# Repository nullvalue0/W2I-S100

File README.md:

S-100 Board Version of Mike Arnold's W2I (WDI to IDE adapter), for emulating up to four 11Mb IMI7710A drives. It is compatible with CDOS, Z80 Cromix, 68000 Cromix and Cromix Plus. It works with the Cromemco WDI and WDI-II controller.

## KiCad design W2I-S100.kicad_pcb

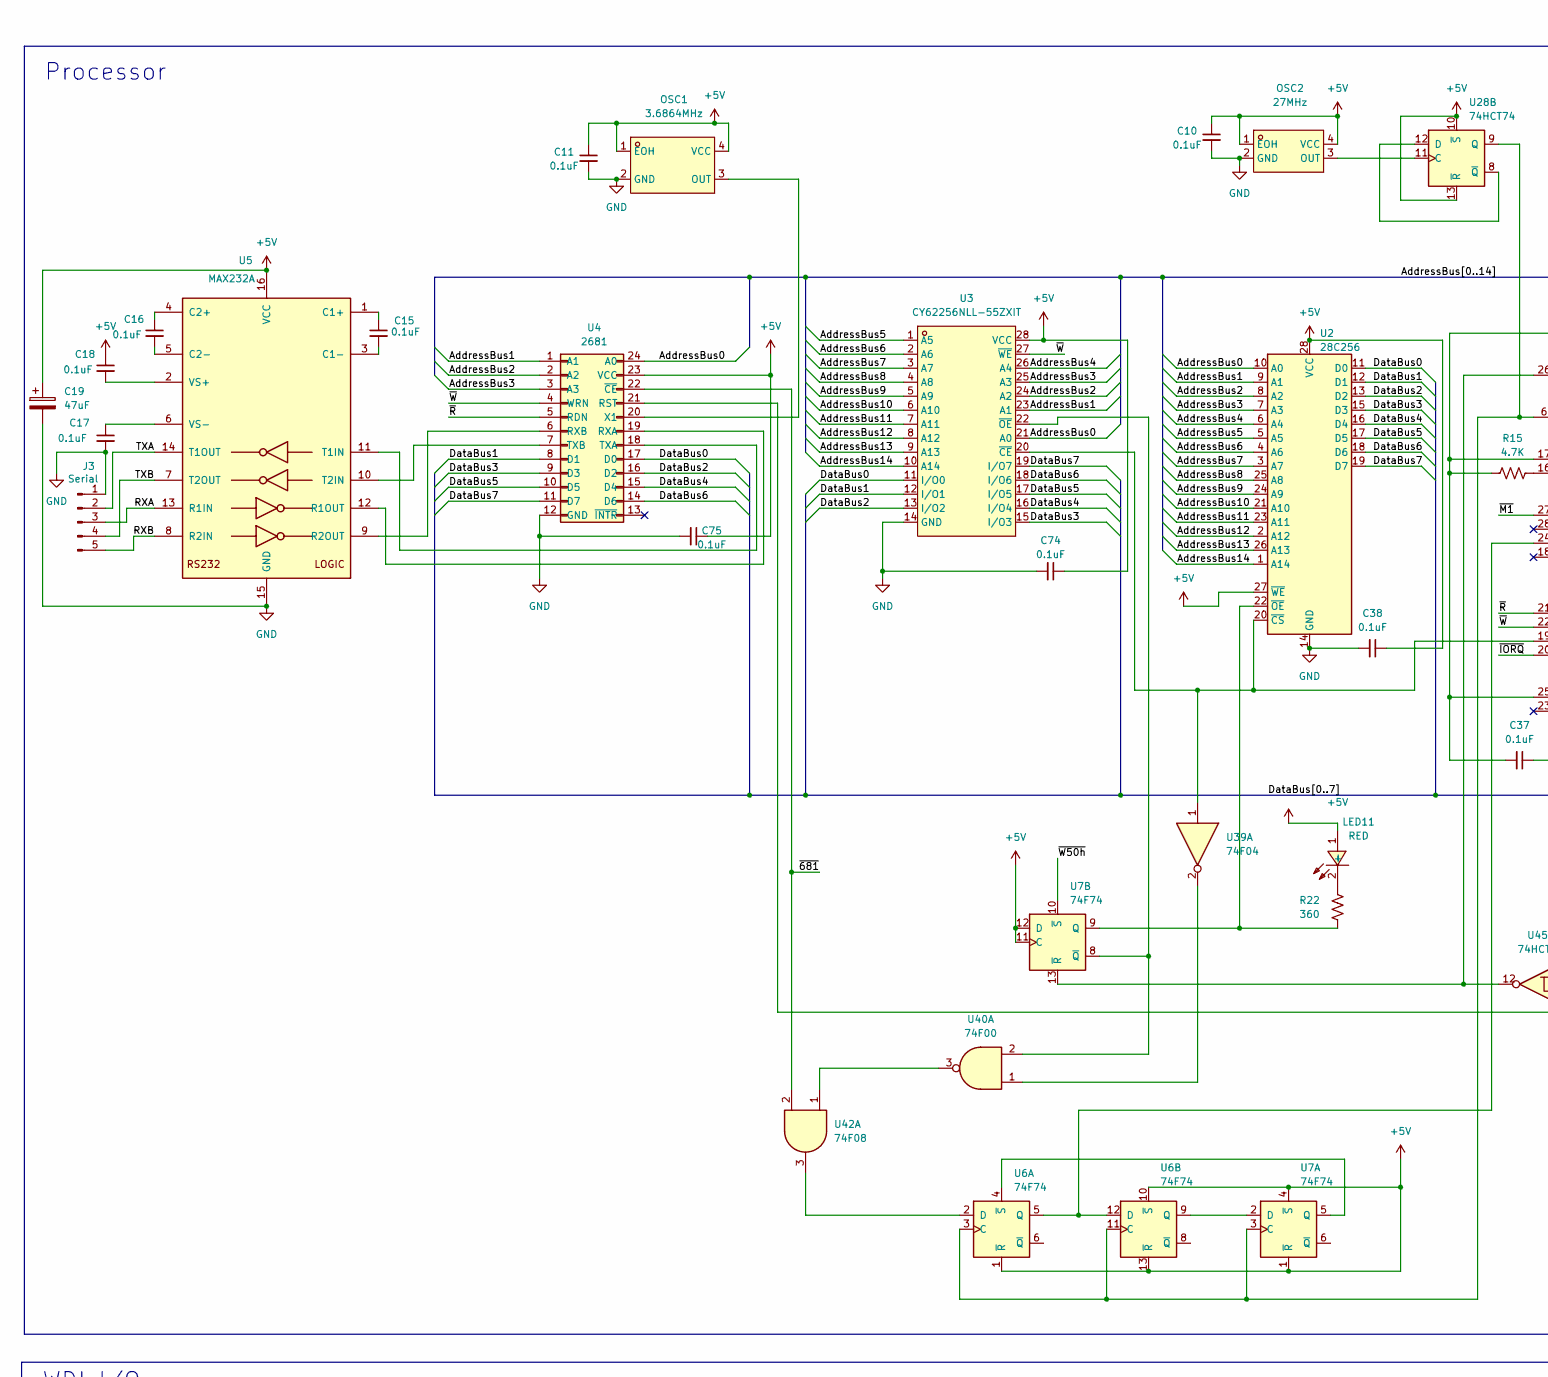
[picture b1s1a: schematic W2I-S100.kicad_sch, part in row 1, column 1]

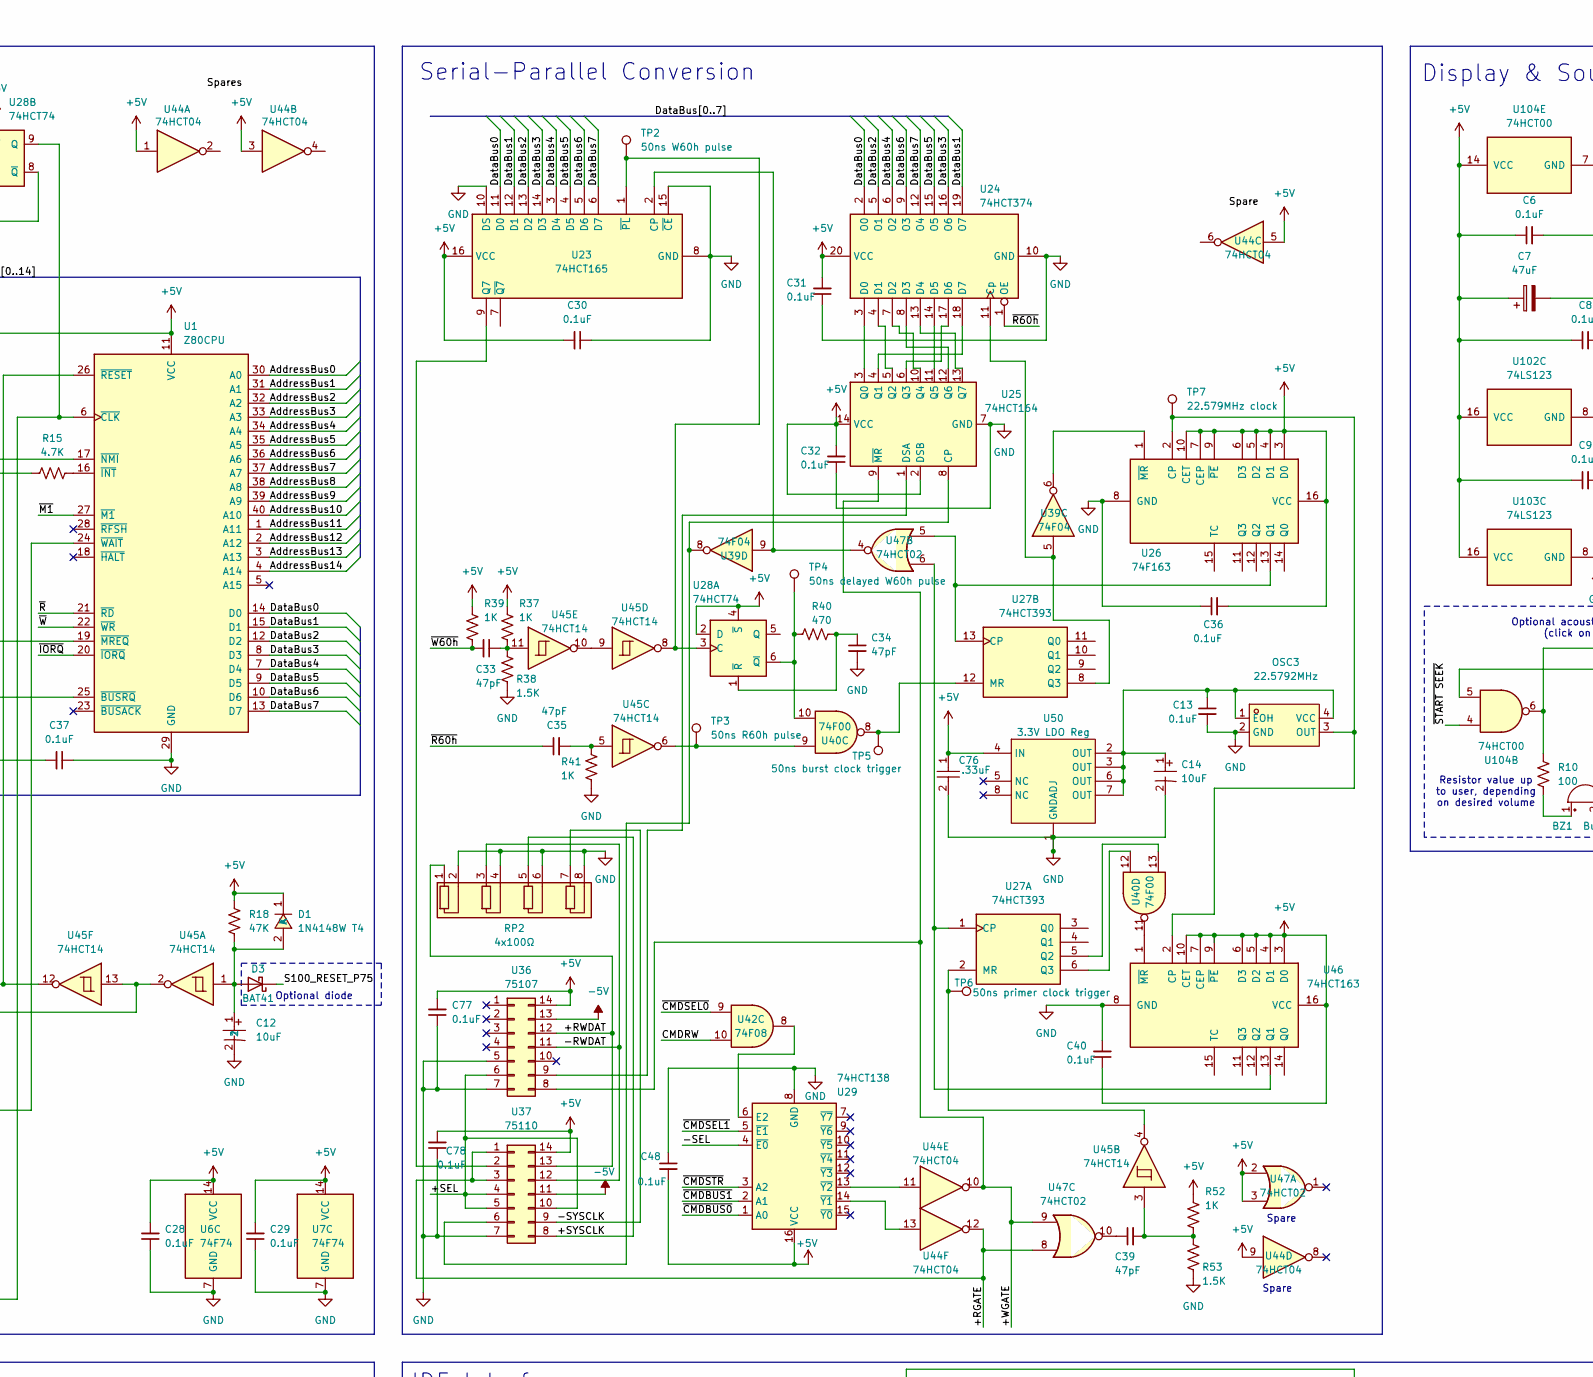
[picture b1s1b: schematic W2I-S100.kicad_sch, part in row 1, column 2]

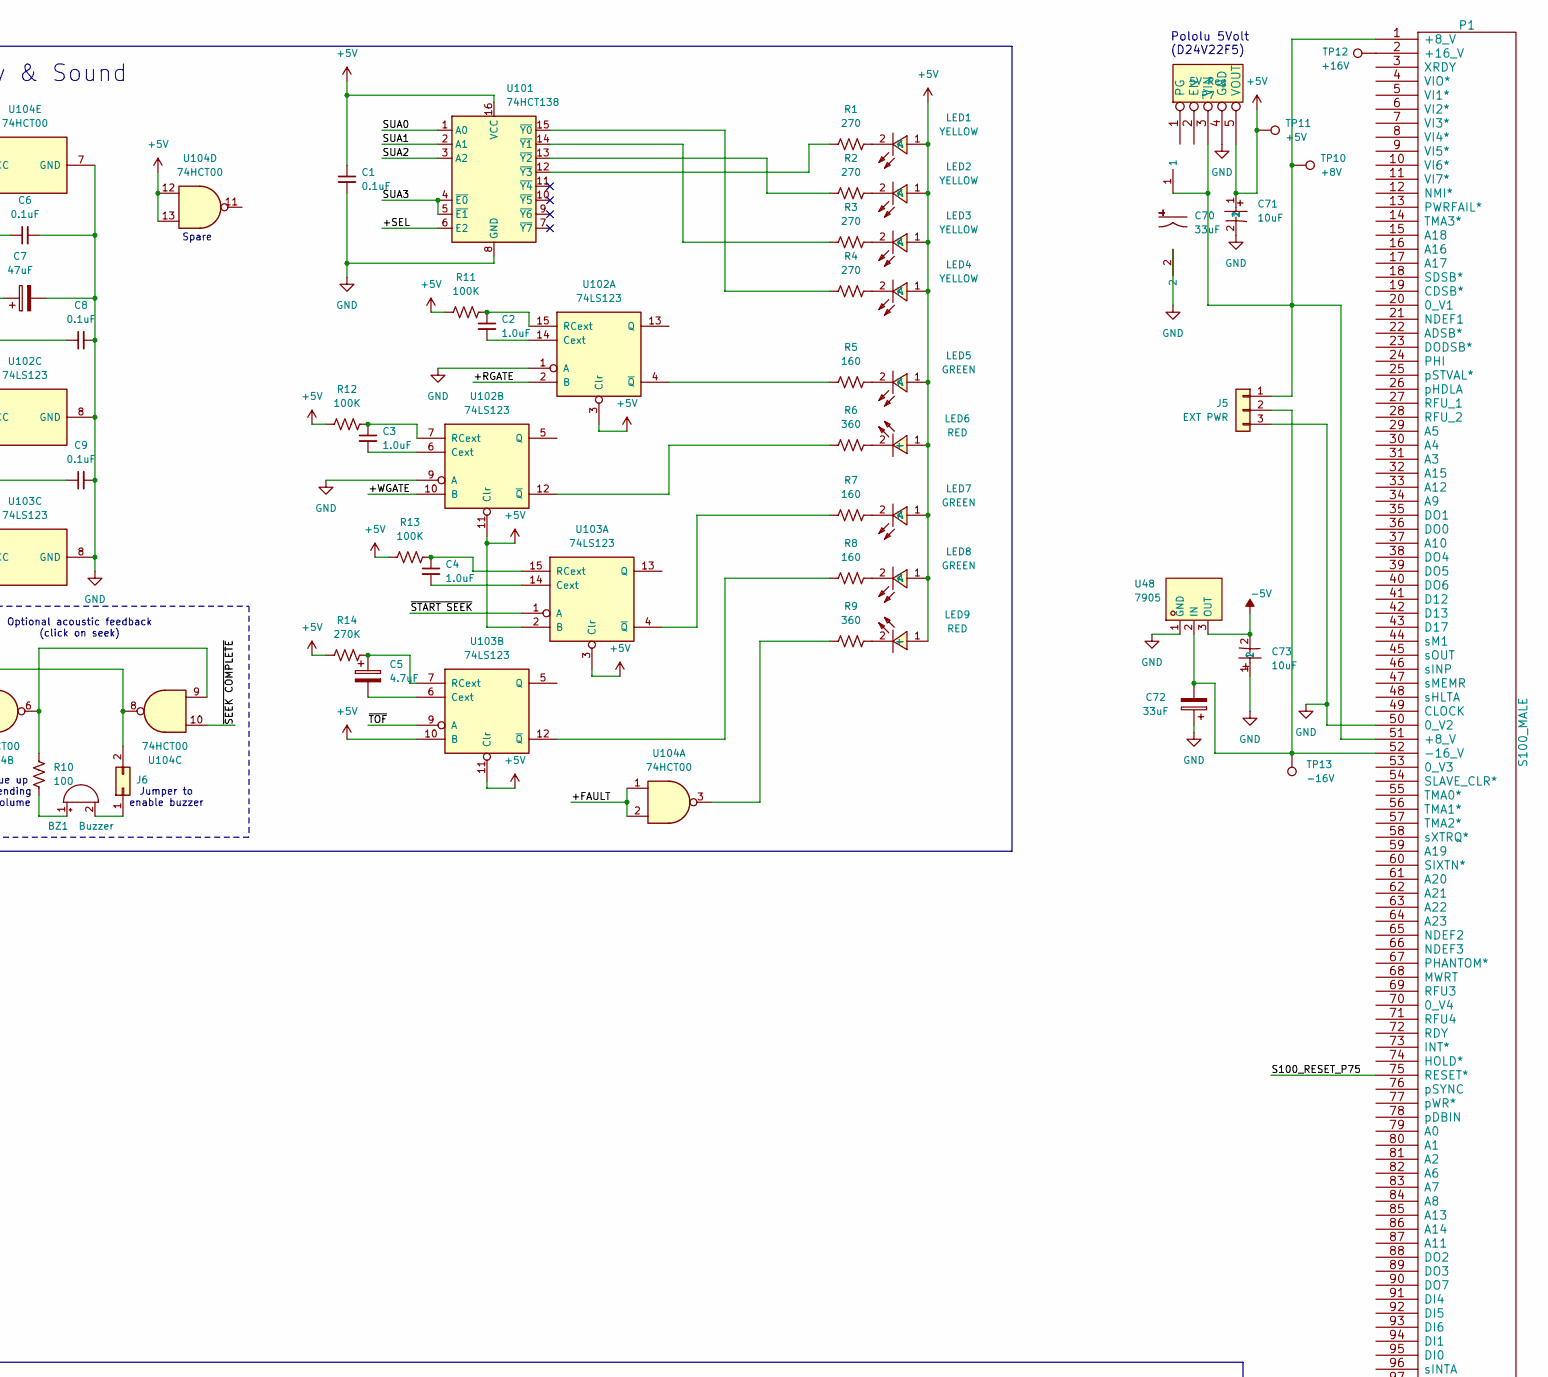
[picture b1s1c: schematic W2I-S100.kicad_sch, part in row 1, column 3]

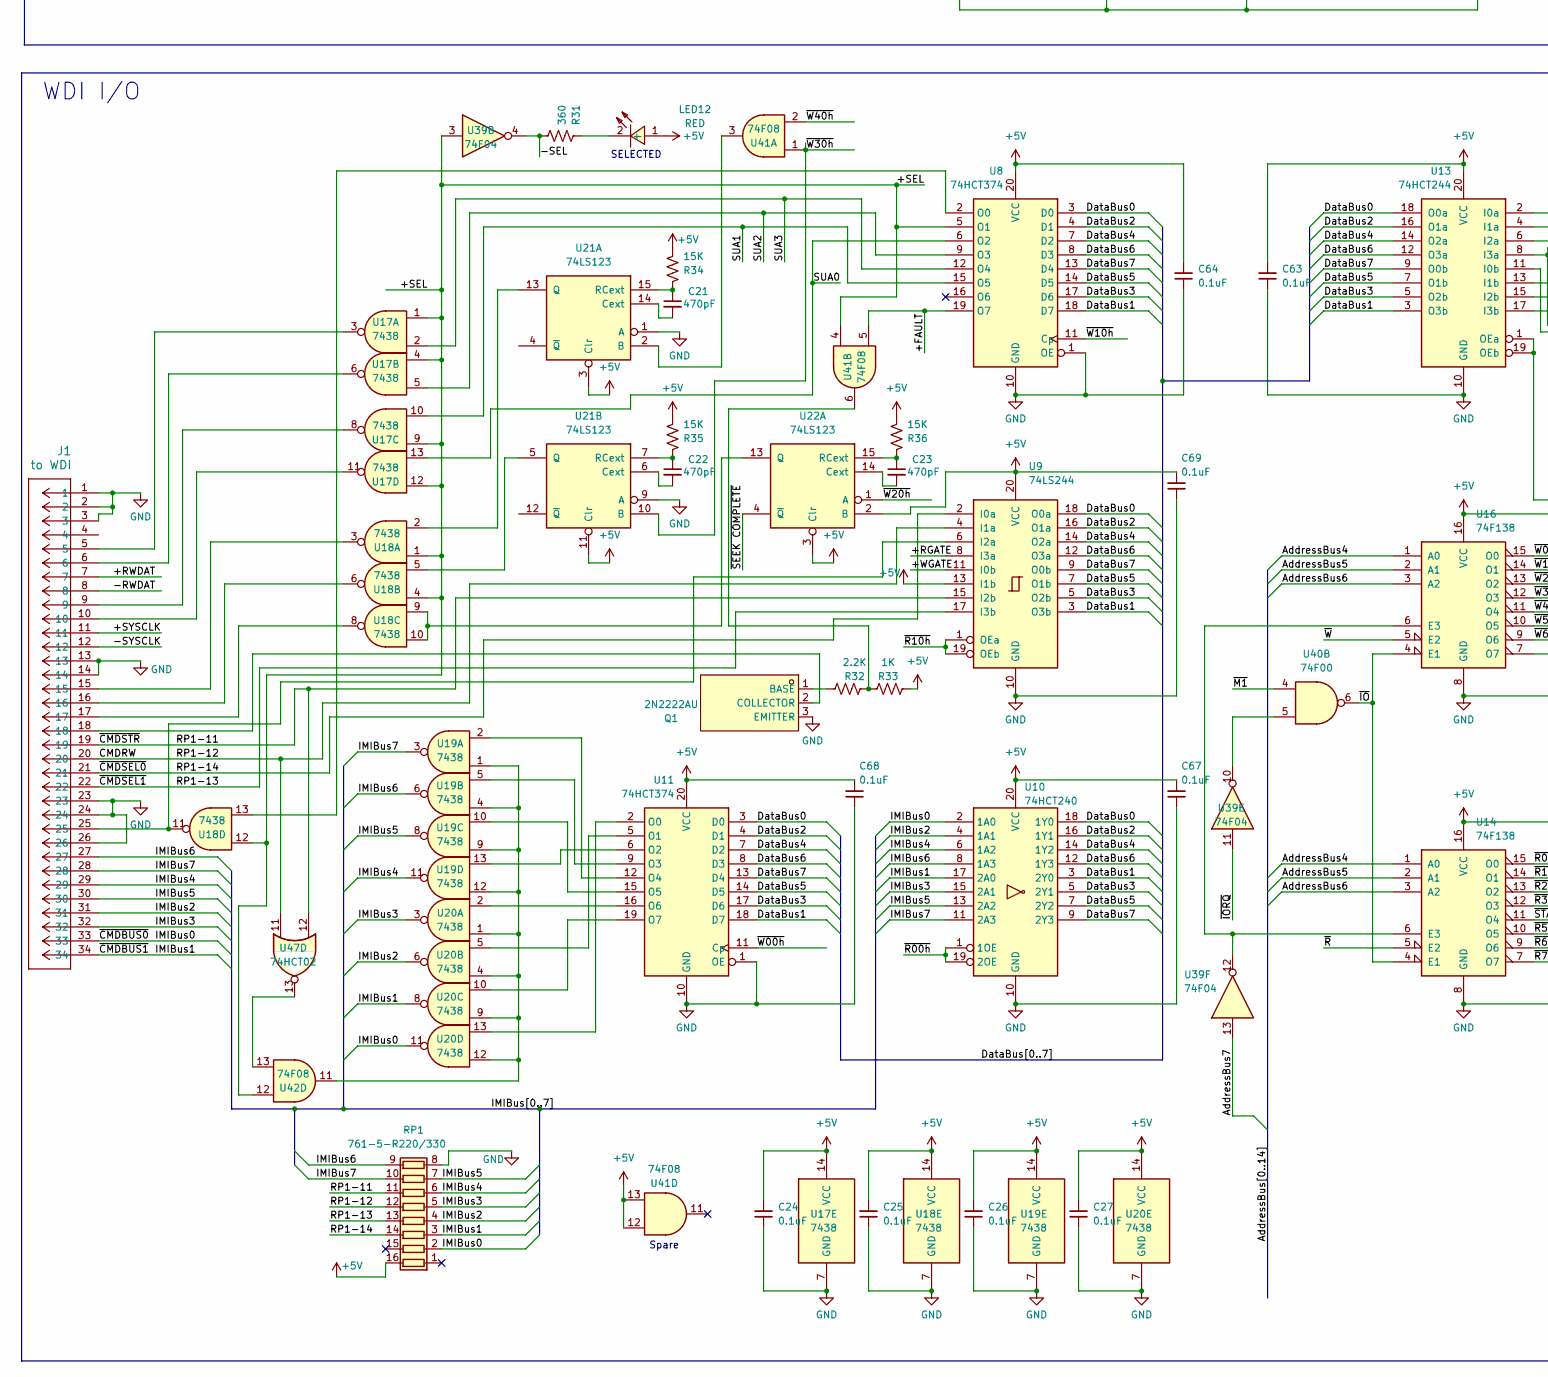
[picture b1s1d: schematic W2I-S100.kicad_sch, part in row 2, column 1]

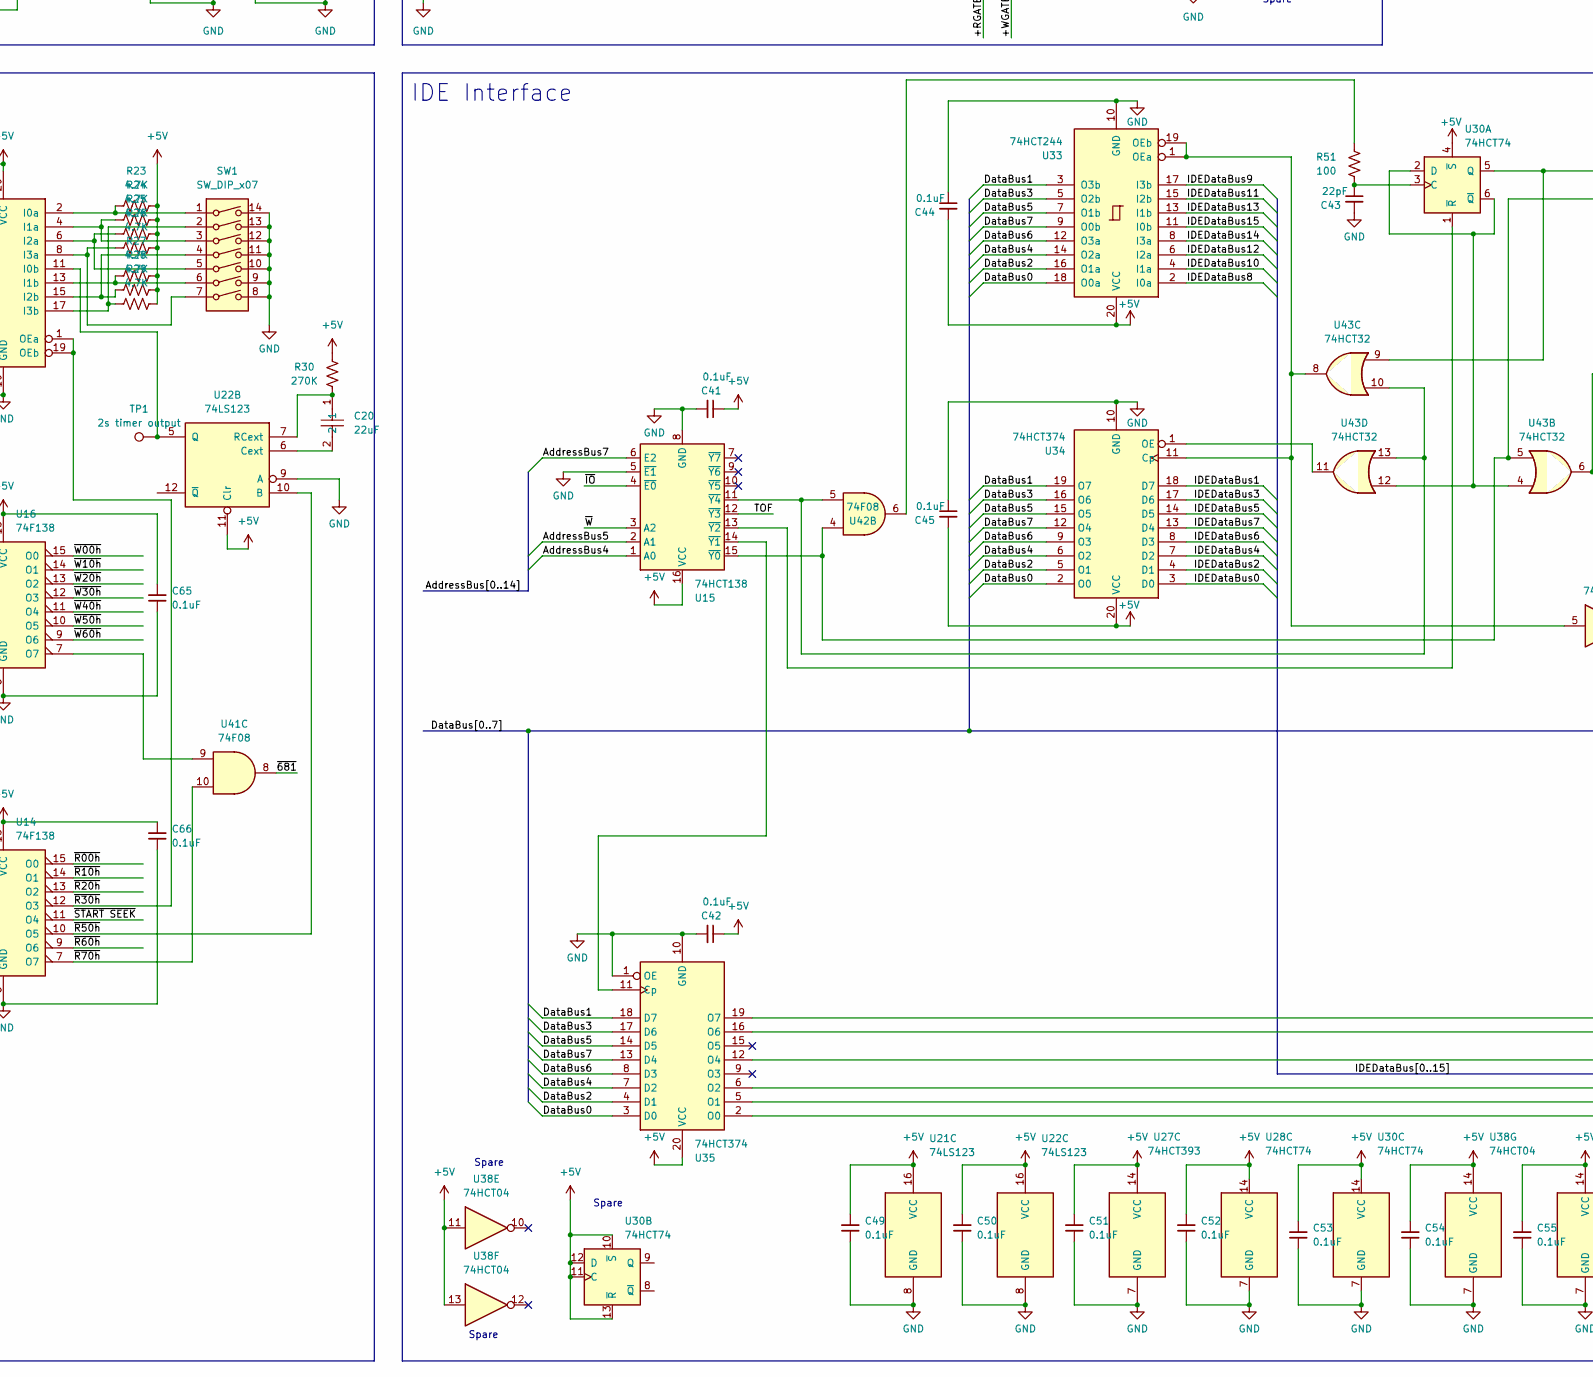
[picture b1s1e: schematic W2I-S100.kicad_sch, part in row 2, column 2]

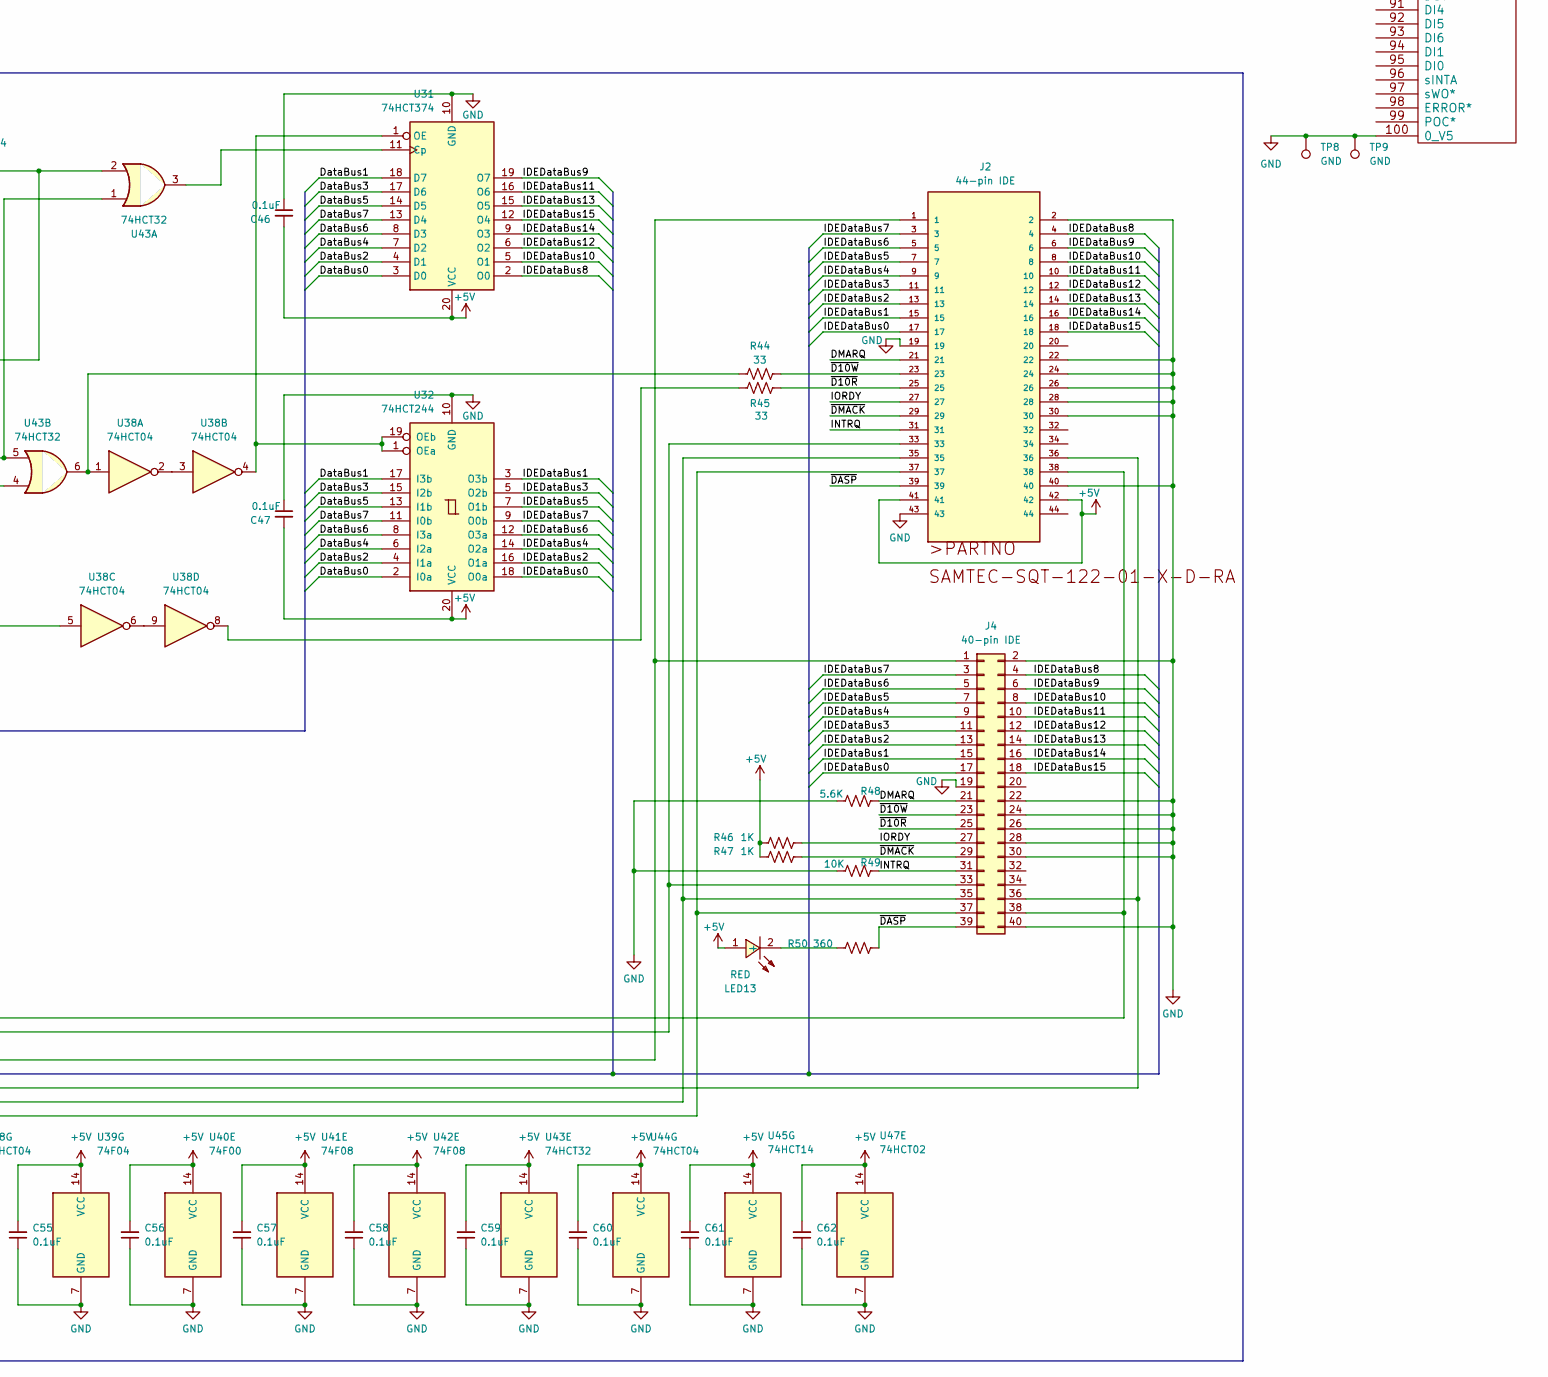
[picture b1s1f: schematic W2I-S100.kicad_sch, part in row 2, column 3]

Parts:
BZ1: Buzzer; Buzzer_12x9.5RM7.6
C1, C6, C8, C9, C10, C11, C13, C15, C16, C17, C18, C24, C25, C26, C27, C28, C29, C30, C31, C32, C36, C37, C38, C40, C41, C42, C44, C45, C46, C47, C48, C49, C50, C51, C52, C53, C54, C55, C56, C57, C58, C59, C60, C61, C62, C63, C64, C65, C66, C67, C68, C69, C74, C75, C77, C78: 0.1uF; C0603; LCSC Part C1590
C2, C3, C4: 1.0uF; C0603; LCSC Part C29936
C5: 4.7uF; CAP-SMD_BD4.0-L4.3-W4.3-LS5.3-FD; LCSC Part C264246
C7, C19: 47uF; CAP-SMD_BD6.3-L6.6-W6.6-FD; LCSC Part C141425
C12, C14, C71, C73: 10uF; CAP-SMD_BD4.0-L4.3-W4.3-FD; LCSC Part C3343
C20: 22uF; C0603; LCSC Part C2762594
C21, C22, C23: 470pF; C0603; LCSC Part C519395
C33, C34, C35, C39: 47pF; C0603; LCSC Part C519392
C43: 22pF; C0603; LCSC Part C519390
C70, C72: 33uF; CAP-SMD_BD6.3-L6.6-W6.6-FD; LCSC Part C249892
C76: .33uF; C0603; LCSC Part C1615
D1: 1N4148W T4; SOD-123_L2.8-W1.8-LS3.7-RD; LCSC Part C2099
D3: BAT41; D_DO-35_SOD27_P7.62mm_Horizontal
J1: to WDI; IDC-Header_2x17_P2.54mm_Vertical
J2: 44-pin IDE; SAMTEC-SQT-122-01-X-D-RA
J3: Serial; PinHeader_1x05_P2.54mm_Vertical
J4: 40-pin IDE; IDC-Header_2x20_P2.54mm_Vertical
J5: EXT PWR; PinHeader_1x03_P2.54mm_Vertical
J6: Jumper to enable buzzer; PinHeader_2x01_P2.54mm_Vertical
LED1, LED2, LED3, LED4: YELLOW; LED0805-R-RD; LCSC Part C84261
LED5, LED7, LED8: GREEN; LED0805-R-RD; LCSC Part C84260
LED6, LED9, LED11, LED12, LED13: RED; LED0805-R-RD; LCSC Part C84256
OSC1: 3.6864MHz; OSC-SMD_4P-L7.0-W5.0-BL-2; LCSC Part C1851439
OSC2: 27MHz; OSC-SMD_4P-L7.0-W5.0-BL-2; LCSC Part C1851667
OSC3: 22.5792MHz; OSC-SMD_4P-L7.0-W5.0-BL-2; LCSC Part C7431407
P1: S100_MALE
P7: 5V Reg; PinHeader_1x05_P2.54mm_Vertical
Q1: 2N2222AU; SOT-89-3_L4.5-W2.4-P1.50-LS4.0-BR; LCSC Part C21714170
R1, R2, R3, R4: 270; R0603; LCSC Part C22966
R5, R7, R8: 160; R0603; LCSC Part C22814
R6, R9, R22, R31, R50: 360; R0603; LCSC Part C25194
R10: 100; R_Axial_DIN0207_L6.3mm_D2.5mm_P10.16mm_Horizontal
R11, R12, R13: 100K; R1206; LCSC Part C17900
R14, R30: 270K; R1206; LCSC Part C17940
R15, R23, R24, R25, R26, R27, R28, R29: 4.7K; R1206; LCSC Part C17936
R18: 47K; R1206; LCSC Part C25833
R32: 2.2K; R1206; LCSC Part C17948
R33, R37, R39, R41, R46, R47, R52: 1K; R1206; LCSC Part C1469
R34, R35, R36: 15K; R1206; LCSC Part C25828
R38, R53: 1.5K; R1206; LCSC Part C26030
R40: 470; R1206; LCSC Part C4502
R44, R45: 33; R1206; LCSC Part C18005
R48: 5.6K; R1206; LCSC Part C18028
R49: 10K; R1206; LCSC Part C17902
R51: 100; R1206; LCSC Part C17901
RP1: 761-5-R220/330; DIP-16_W7.62mm
RP2: 4x100Ω; R_Array_SIP8
SW1: SW_DIP_x07; DIP-14_W7.62mm
TP1: 2s timer output; TestPoint_THTPad_2.0x2.0mm_Drill1.0mm
TP2: 50ns W60h pulse; TestPoint_THTPad_2.0x2.0mm_Drill1.0mm
TP3: 50ns R60h pulse; TestPoint_THTPad_2.0x2.0mm_Drill1.0mm
TP4: 50ns delayed W60h pulse; TestPoint_THTPad_2.0x2.0mm_Drill1.0mm
TP5: 50ns burst clock trigger; TestPoint_THTPad_2.0x2.0mm_Drill1.0mm
TP6: 50ns primer clock trigger; TestPoint_THTPad_2.0x2.0mm_Drill1.0mm
TP7: 22.579MHz clock; TestPoint_THTPad_2.0x2.0mm_Drill1.0mm
TP8, TP9: GND; TestPoint_THTPad_2.0x2.0mm_Drill1.0mm
TP10: +8V; TestPoint_THTPad_2.0x2.0mm_Drill1.0mm
TP11: +5V; TestPoint_THTPad_2.0x2.0mm_Drill1.0mm
TP12: +16V; TestPoint_THTPad_2.0x2.0mm_Drill1.0mm
TP13: -16V; TestPoint_THTPad_2.0x2.0mm_Drill1.0mm
U1: Z80CPU; DIP-40_W15.24mm
U2: 28C256; DIP-28_W15.24mm
U3: CY62256NLL-55ZXIT; TSOP-28_L11.8-W8.0-P0.55-LS13.4-B_CYPRESS; LCSC Part C2759940
U4: 2681; DIP-24_W10.16mm
U5: MAX232A; DIP-16_W7.62mm
U6, U7: 74F74; SOIC-14_L8.7-W3.9-P1.27-LS6.0-BL; LCSC Part C6805
U8, U11, U24, U31, U34, U35: 74HCT374; SOP-20_L12.6-W5.3-P1.27-LS7.8-BL; LCSC Part C2677828
U9: 74LS244; SOP-20_L12.6-W5.3-P1.27-LS7.8-BL; LCSC Part C22374097
U10: 74HCT240; TSSOP-20_L6.5-W4.4-P0.65-LS6.5-BL; LCSC Part C543088
U13, U32, U33: 74HCT244; TSSOP-20_L6.5-W4.4-P0.65-LS6.4-BL; LCSC Part C131088
U14, U16: 74F138; DIP-16_W7.62mm
U15, U29, U101: 74HCT138; TSSOP-16_L5.0-W4.4-P0.65-LS6.4-BL; LCSC Part C8115
U17, U18, U19, U20: 7438; DIP-14_W7.62mm
U21, U22, U102, U103: 74LS123; SOIC-16_L9.9-W3.9-P1.27-LS6.0-BL; LCSC Part C234231
U23: 74HCT165; SOIC-16_L9.9-W3.9-P1.27-LS6.0-BL; LCSC Part C456131
U25: 74HCT164; TSSOP-14_L5.0-W4.4-P0.65-LS6.4-BL; LCSC Part C2908835
U26: 74F163; SOIC-16_L9.9-W3.9-P1.27-LS6.0-BL; LCSC Part C2675415
U27: 74HCT393; SO-14_L8.7-W3.9-P1.27-LS6.0-BL; LCSC Part C547642
U28, U30: 74HCT74; SO-14_L8.9-W3.9-P1.27-LS6.0-BL; LCSC Part C686657
U36: 75107; DIP-14_W7.62mm
U37: 75110; DIP-14_W7.62mm
U38, U44: 74HCT04; TSSOP-14_L5.0-W4.4-P0.65-LS6.4-BL; LCSC Part C131695
U39: 74F04; SOIC-14_L8.7-W3.9-P1.27-LS6.0-BL; LCSC Part C7159
U40: 74F00; SOIC-14_L8.7-W3.9-P1.27-LS6.0-BL; LCSC Part C7158
U41, U42: 74F08; SSOP-14_L6.2-W5.3-P0.65-LS7.8-BL-1; LCSC Part C4469192
U43: 74HCT32; TSSOP-14_L5.0-W4.4-P0.65-LS6.4-BL; LCSC Part C547595
U45: 74HCT14; TSSOP-14_L5.0-W4.4-P0.65-LS6.4-BL; LCSC Part C5968
U46: 74HCT163; SOIC-16_L9.9-W3.9-P1.27-LS6.0-BL; LCSC Part C2866759
U47: 74HCT02; SOIC-14_L8.7-W3.9-P1.27-LS6.0-BL; LCSC Part C471050
U48: 7905; TO-252-2_L6.6-W6.1-P4.57-LS10.1-BR-CW; LCSC Part C19273129
U50: 3.3V LDO Reg; SOIC-8_L5.0-W4.0-P1.27-LS6.0-BL; LCSC Part C7301
U104: 74HCT00; TSSOP-14_L5.0-W4.4-P0.65-LS6.4-BL; LCSC Part C8206

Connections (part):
+5V: C1.1, C6.1, C7.1, C8.1, C9.1, C10.1, C11.1, C18.1, C19.1, C24.2, C25.2, C26.2, C27.2, C28.2, C29.2, C30.2, C31.2, C32.2, C36.2, C37.2, C38.1, C40.1, C41.1, C42.1, C44.2, C45.2, C46.2, C47.2, C48.2, C49.2, C50.2, C51.2, C52.2, C53.2, C54.2, C55.2, C56.2, C57.2, C58.2, C59.2, C60.2, C61.2, C62.2, C63.2, C64.2, C65.2, C66.2, C67.2, C68.2, C69.2, C71.1, C74.1, C75.1, C76.1, C77.2, C78.2, D1.1 (K), J2.41, J2.42, LED1.1 (A), LED2.1 (A), LED3.1 (A), LED4.1 (A), LED5.1 (A), LED6.1 (+), LED7.1 (A), LED8.1 (A), LED9.1 (+), LED11.1 (+), LED12.1 (+), LED13.1 (+), OSC1.1 (EOH), OSC1.4 (VCC), OSC2.1 (EOH), OSC2.4 (VCC), P7.5 (VOUT), R11.2, R12.2, R13.2, R14.2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
-5V: C73.2, U36.13, U37.11, U48.3 (OUT)
/+FAULT: U8.19 (O7), U41.5, U104.1, U104.2
/+RGATE: U9.8 (I3a), U37.1, U37.3, U44.12, U47.8, U102.2 (B)
/+RWDAT: J1.7, RP2.1 (R1.1), U36.12, U37.13
/+SEL: U8.5 (O1), U17.1, U17.4, U17.9, U17.12, U18.1, U18.4, U18.12, U36.6, U37.4, U37.5, U37.10, U39.3, U41.4, U42.12, U101.6 (E2)
/+SYSCLK: J1.11, RP2.5 (R3.1), U37.8
/+WGATE: U9.11 (I0b), U25.9 (~MR), U36.8, U44.10, U47.9, U102.10 (B)
/-RWDAT: J1.8, RP2.3 (R2.1), U36.11, U37.12
/-SEL: R31.2, U29.4 (~E0), U39.4
/-SYSCLK: J1.12, RP2.7 (R4.1), U37.9
/AddressBus0: U1.30 (A0), U2.10 (A0), U3.21 (A0), U4.24 (A0)
/AddressBus1: U1.31 (A1), U2.9 (A1), U3.23 (A1), U4.1 (A1)
/AddressBus2: U1.32 (A2), U2.8 (A2), U3.24 (A2), U4.2 (A2)
/AddressBus3: U1.33 (A3), U2.7 (A3), U3.25 (A3), U4.3 (A3)
/AddressBus4: U1.34 (A4), U2.6 (A4), U3.26 (A4), U14.1 (A0), U15.1 (A0), U16.1 (A0)
/AddressBus5: U1.35 (A5), U2.5 (A5), U3.1 (A5), U14.2 (A1), U15.2 (A1), U16.2 (A1)
/AddressBus6: U1.36 (A6), U2.4 (A6), U3.2 (A6), U14.3 (A2), U16.3 (A2)
/AddressBus7: U1.37 (A7), U2.3 (A7), U3.3 (A7), U15.6 (E2), U39.13
/AddressBus8: U1.38 (A8), U2.25 (A8), U3.4 (A8)
/AddressBus9: U1.39 (A9), U2.24 (A9), U3.5 (A9)
/AddressBus10: U1.40 (A10), U2.21 (A10), U3.6 (A10)
/AddressBus11: U1.1 (A11), U2.23 (A11), U3.7 (A11)
/AddressBus12: U1.2 (A12), U2.2 (A12), U3.8 (A12)
/AddressBus13: U1.3 (A13), U2.26 (A13), U3.9 (A13)
/AddressBus14: U1.4 (A14), U2.1 (A14), U3.10 (A14)
/CMDRW: J1.20, RP1.12 (R5.2), U9.4 (I1a), U42.10, U47.11
/DMARQ: J2.21, J4.21, R48.2
/DataBus0: U1.14 (D0), U2.11 (D0), U3.11 (I/O0), U4.17 (D0), U8.3 (D0), U9.18 (O0a), U10.18 (1Y0), U11.3 (D0), U13.18 (O0a), U23.11 (D0), U24.2 (O0), U31.3 (D0), U32.2 (I0a), U33.18 (O0a), U34.2 (O0), U35.3 (D0)
/DataBus1: U1.15 (D1), U2.12 (D1), U3.12 (I/O1), U4.8 (D1), U8.18 (D7), U9.3 (O3b), U10.3 (2Y0), U11.18 (D7), U13.3 (O3b), U23.12 (D1), U24.19 (O7), U31.18 (D7), U32.17 (I3b), U33.3 (O3b), U34.19 (O7), U35.18 (D7)
/DataBus2: U1.12 (D2), U2.13 (D2), U3.13 (I/O2), U4.16 (D2), U8.4 (D1), U9.16 (O1a), U10.16 (1Y1), U11.4 (D1), U13.16 (O1a), U23.13 (D2), U24.5 (O1), U31.4 (D1), U32.4 (I1a), U33.16 (O1a), U34.5 (O1), U35.4 (D1)
/DataBus3: U1.8 (D3), U2.15 (D3), U3.15 (I/O3), U4.9 (D3), U8.17 (D6), U9.5 (O2b), U10.5 (2Y1), U11.17 (D6), U13.5 (O2b), U23.14 (D3), U24.16 (O6), U31.17 (D6), U32.15 (I2b), U33.5 (O2b), U34.16 (O6), U35.17 (D6)
/DataBus4: U1.7 (D4), U2.16 (D4), U3.16 (I/O4), U4.15 (D4), U8.7 (D2), U9.14 (O2a), U10.14 (1Y2), U11.7 (D2), U13.14 (O2a), U23.3 (D4), U24.6 (O2), U31.7 (D2), U32.6 (I2a), U33.14 (O2a), U34.6 (O2), U35.7 (D2)
/DataBus5: U1.9 (D5), U2.17 (D5), U3.17 (I/O5), U4.10 (D5), U8.14 (D5), U9.7 (O1b), U10.7 (2Y2), U11.14 (D5), U13.7 (O1b), U23.4 (D5), U24.15 (O5), U31.14 (D5), U32.13 (I1b), U33.7 (O1b), U34.15 (O5), U35.14 (D5)
/DataBus6: U1.10 (D6), U2.18 (D6), U3.18 (I/O6), U4.14 (D6), U8.8 (D3), U9.12 (O3a), U10.12 (1Y3), U11.8 (D3), U13.12 (O3a), U23.5 (D6), U24.9 (O3), U31.8 (D3), U32.8 (I3a), U33.12 (O3a), U34.9 (O3), U35.8 (D3)
/DataBus7: U1.13 (D7), U2.19 (D7), U3.19 (I/O7), U4.11 (D7), U8.13 (D4), U9.9 (O0b), U10.9 (2Y3), U11.13 (D4), U13.9 (O0b), U23.6 (D7), U24.12 (O4), U31.13 (D4), U32.11 (I0b), U33.9 (O0b), U34.12 (O4), U35.13 (D4)
/IDEDataBus0: J2.17, J4.17, U32.18 (O0a), U34.3 (D0)
/IDEDataBus1: J2.15, J4.15, U32.3 (O3b), U34.18 (D7)
/IDEDataBus2: J2.13, J4.13, U32.16 (O1a), U34.4 (D1)
/IDEDataBus3: J2.11, J4.11, U32.5 (O2b), U34.17 (D6)
/IDEDataBus4: J2.9, J4.9, U32.14 (O2a), U34.7 (D2)
/IDEDataBus5: J2.7, J4.7, U32.7 (O1b), U34.14 (D5)
/IDEDataBus6: J2.5, J4.5, U32.12 (O3a), U34.8 (D3)
/IDEDataBus7: J2.3, J4.3, U32.9 (O0b), U34.13 (D4)
/IDEDataBus8: J2.4, J4.4, U31.2 (O0), U33.2 (I0a)
/IDEDataBus9: J2.6, J4.6, U31.19 (O7), U33.17 (I3b)
/IDEDataBus10: J2.8, J4.8, U31.5 (O1), U33.4 (I1a)
/IDEDataBus11: J2.10, J4.10, U31.16 (O6), U33.15 (I2b)
/IDEDataBus12: J2.12, J4.12, U31.6 (O2), U33.6 (I2a)
/IDEDataBus13: J2.14, J4.14, U31.15 (O5), U33.13 (I1b)
/IDEDataBus14: J2.16, J4.16, U31.9 (O3), U33.8 (I3a)
/IDEDataBus15: J2.18, J4.18, U31.12 (O4), U33.11 (I0b)
/IMIBus0: J1.33, RP1.2 (R2.1), U10.2 (1A0), U20.11, U29.1 (A0)
/IMIBus1: J1.34, RP1.3 (R3.1), U10.17 (2A0), U20.8, U29.2 (A1)
/IMIBus2: J1.31, RP1.4 (R4.1), U10.4 (1A1), U20.6
/IMIBus3: J1.32, RP1.5 (R5.1), U10.15 (2A1), U20.3
/IMIBus4: J1.29, RP1.6 (R6.1), U10.6 (1A2), U19.11
/IMIBus5: J1.30, RP1.7 (R7.1), U10.13 (2A2), U19.8
/IMIBus6: J1.27, RP1.9 (R8.2), U10.8 (1A3), U19.6
/IMIBus7: J1.28, RP1.10 (R7.2), U10.11 (2A3), U19.3
/INTRQ: J2.31, J4.31, R49.2
/IORDY: J2.27, J4.27, R46.2
/RP1-11: J1.19, RP1.11 (R6.2), U9.15 (I2b), U29.3 (A2), U47.12
/RP1-13: J1.22, RP1.13 (R4.2), U9.17 (I3b), U29.5 (~E1)
/RP1-14: J1.21, RP1.14 (R3.2), U9.2 (I0a), U42.9
/RXA: J3.3, U5.13 (R1IN)
/RXB: J3.5, U5.8 (R2IN)
/S100_RESET_P75: D3.1 (K), P1.75 (RESET*)
/SUA0: U8.6 (O2), U17.13, U101.1 (A0)
/SUA1: U8.15 (O5), U17.10, U101.2 (A1)
/SUA2: U8.9 (O3), U17.5, U101.3 (A2)
/SUA3: U8.12 (O4), U17.2, U101.4 (~E0), U101.5 (~E1)
/TOF: U15.12 (~Y3)
/TXA: J3.2, U5.14 (T1OUT)
/TXB: J3.4, U5.7 (T2OUT)
/~681: U4.22 (~CE), U41.8, U42.2
/~D10R: J2.25, J4.25, R45.1
/~D10W: J2.23, J4.23, R44.1
/~DASP: J2.39, J4.39, R50.1
/~DMACK: J2.29, J4.29, R47.2
/~IORQ: U1.20 (~IORQ), U39.11
/~IO: U14.4 (E1), U15.4 (~E0), U16.4 (E1), U40.6
/~M1: U1.27 (~M1), U40.4
/~R00h: U10.1 (1OE), U10.19 (2OE), U14.15 (O0)
/~R10h: U9.1 (OEa), U9.19 (OEb), U14.14 (O1)
/~R20h: U14.13 (O2)
/~R30h: U13.1 (OEa), U13.19 (OEb), U14.12 (O3)
/~R50h: U14.10 (O5), U22.10 (B)
/~R60h: C35.1, U14.9 (O6), U24.1 (OE)
/~R70h: U14.7 (O7), U41.10
/~R: U1.21 (~RD), U4.5 (RDN), U14.5 (E2)
/~SEEK COMPLETE: U22.4 (~Q), U104.10
/~START SEEK: U14.11 (O4), U103.1 (A), U104.4
/~TOF: U103.9 (A)
/~W00h: U11.11 (Cp), U16.15 (O0)
/~W10h: U8.11 (Cp), U16.14 (O1)
/~W20h: U16.13 (O2), U22.1 (A)
/~W30h: U16.12 (O3), U21.10 (B), U41.1
/~W40h: U16.11 (O4), U41.2
/~W50h: U7.10 (~S), U16.10 (O5)
/~W60h: C33.2, R39.2, U16.9 (O6)
/~W: U1.22 (~WR), U3.27 (~WE), U4.4 (WRN), U15.3 (A2), U16.5 (E2)
GND: C1.2, C6.2, C7.2, C8.2, C9.2, C10.2, C11.2, C12.2, C13.2, C14.2, C17.2, C19.2, C24.1, C25.1, C26.1, C27.1, C28.1, C29.1, C30.1, C31.1, C32.1, C34.2, C36.1, C37.1, C38.2, C40.2, C41.2, C42.2, C43.2, C44.1, C45.1, C46.1, C47.1, C48.1, C49.1, C50.1, C51.1, C52.1, C53.1, C54.1, C55.1, C56.1, C57.1, C58.1, C59.1, C60.1, C61.1, C62.1, C63.1, C64.1, C65.1, C66.1, C67.1, C68.1, C69.1, C70.2, C71.2, C72.1, C73.1, C74.2, C75.2, C76.2, C77.1, C78.1, J1.1, J1.2, J1.3, J1.13, J1.14, J1.23, J1.24, J1.26, J2.2, J2.19, J2.22, J2.24, J2.26, J2.28, J2.30, J2.40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
unnamed: BZ1.1 (+), R10.2
unnamed: BZ1.2 (-), J6.1
unnamed: C33.1, R37.2, R38.1, U45.11
unnamed: C35.2, R41.2, U45.5
unnamed: C39.1, U47.10
unnamed: C39.2, R52.2, R53.1, U45.3
unnamed: C12.1, D1.2 (A), D3.2 (A), R18.1, U45.1
unnamed: J1.5, U17.3
unnamed: J1.6, U17.6
unnamed: J1.9, U17.8
unnamed: J1.10, U17.11
unnamed: J1.15, U18.3
unnamed: J1.16, U18.6
unnamed: J1.17, U18.8
unnamed: J2.1, J4.1, U35.12 (O4)
unnamed: J2.33, J4.33, U35.16 (O6)
unnamed: J2.35, J4.35, U35.5 (O1)
unnamed: J2.36, J4.36, U35.6 (O2)
unnamed: J2.37, J4.37, U35.2 (O0)
unnamed: J2.38, J4.38, U35.19 (O7)
unnamed: C70.1, J5.1, P1.1 (+8_V), P1.51 (+8_V), P7.3 (VIN), TP10.1
unnamed: C72.2, J5.2, P1.52 (-16_V), TP13.1, U48.2 (IN)
unnamed: J6.2, U104.5, U104.8
unnamed: LED1.2 (K), R1.2
unnamed: LED2.2 (K), R2.2
unnamed: LED3.2 (K), R3.2
unnamed: LED4.2 (K), R4.2
unnamed: LED5.2 (K), R5.2
unnamed: LED6.2 (-), R6.2
unnamed: LED7.2 (K), R7.2
unnamed: LED8.2 (K), R8.2
unnamed: LED9.2 (-), R9.2
unnamed: LED11.2 (-), R22.2
unnamed: LED12.2 (-), R31.1
unnamed: LED13.2 (-), R50.2
unnamed: OSC1.3 (OUT), U4.20 (X1)
unnamed: OSC2.3 (OUT), U28.11 (C)
unnamed: C13.1, C14.1, OSC3.1 (EOH), OSC3.4 (VCC), U50.2 (OUT), U50.3 (OUT), U50.6 (OUT), U50.7 (OUT)
unnamed: OSC3.3 (OUT), TP7.1, U26.2 (CP), U46.2 (CP)
unnamed: P1.2 (+16_V), TP12.1
unnamed: Q1.1 (BASE), R32.2
unnamed: J1.18, Q1.2 (COLLECTOR)
unnamed: R9.1, U104.3
unnamed: R10.1, U104.6, U104.9
unnamed: R32.1, R33.2, U41.6
unnamed: R44.2, U38.1, U43.6
unnamed: R45.2, U38.8
unnamed: R51.1, U42.6
unnamed: TP3.1, U40.9, U45.6
unnamed: U1.6 (~CLK), U6.3 (C), U6.11 (C), U7.3 (C), U28.9 (Q)
unnamed: R15.2, U1.16 (~INT)
unnamed: U1.19 (~MREQ), U2.20 (~CS), U3.20 (~CE), U39.1
unnamed: U1.26 (~RESET), U7.13 (~R), U45.12
unnamed: U1.24 (~WAIT), U6.5 (Q), U6.12 (D)
unnamed: R22.1, U2.22 (~OE), U7.9 (Q)
unnamed: U3.22 (~OE), U7.8 (~Q), U40.2
unnamed: U4.21 (RST), U45.2, U45.13
unnamed: U4.19 (RXA), U5.12 (R1OUT)
unnamed: U4.6 (RXB), U5.9 (R2OUT)
unnamed: U4.18 (TXA), U5.11 (T1IN)
unnamed: U4.7 (TXB), U5.10 (T2IN)
unnamed: C15.1, U5.1 (C1+)
unnamed: C15.2, U5.3 (C1-)
unnamed: C16.1, U5.4 (C2+)
unnamed: C16.2, U5.5 (C2-)
unnamed: C18.2, U5.2 (VS+)
unnamed: C17.1, U5.6 (VS-)
unnamed: U6.2 (D), U42.3
unnamed: U6.4 (~S), U7.5 (Q)
unnamed: U6.9 (Q), U7.2 (D)
unnamed: U8.2 (O0), U18.13
unnamed: J1.25, U9.6 (I2a), U18.11
unnamed: U11.2 (O0), U20.13
unnamed: U11.5 (O1), U20.5
unnamed: U11.6 (O2), U19.13
unnamed: U11.9 (O3), U19.5
unnamed: U11.12 (O4), U19.2
unnamed: U11.15 (O5), U19.10
unnamed: U11.16 (O6), U20.2
unnamed: U11.19 (O7), U20.10
unnamed: R23.2, SW1.1, U13.2 (I0a)
unnamed: TP1.1, U13.11 (I0b), U22.5 (Q)
unnamed: R24.2, SW1.3, U13.4 (I1a)
unnamed: R27.2, SW1.6, U13.13 (I1b)
unnamed: R25.2, SW1.5, U13.6 (I2a)
unnamed: R28.2, SW1.4, U13.15 (I2b)
unnamed: R26.2, SW1.7, U13.8 (I3a)
unnamed: R29.2, SW1.2, U13.17 (I3b)
unnamed: U14.6 (E3), U16.6 (E3), U39.12
unnamed: U15.15 (~Y0), U42.4, U43.1, U43.5
unnamed: U15.14 (~Y1), U35.11 (Cp)
unnamed: U15.13 (~Y2), U30.1 (~R)
unnamed: U15.11 (~Y4), U42.5, U43.10, U43.13
unnamed: U16.7 (O7), U41.9
unnamed: U19.1, U19.4, U19.9, U19.12, U20.1, U20.4, U20.9, U20.12, U42.11
unnamed: U21.2 (B), U41.3
unnamed: C21.2, U21.14 (Cext)
unnamed: U18.2, U21.13 (Q)
unnamed: C21.1, R34.2, U21.15 (RCext)
unnamed: C22.2, U21.6 (Cext)
unnamed: U18.5, U21.5 (Q)
unnamed: C22.1, R35.2, U21.7 (RCext)
unnamed: C23.2, U22.14 (Cext)
unnamed: U18.9, U18.10, U22.13 (Q)
unnamed: C23.1, R36.2, U22.15 (RCext)
unnamed: C20.2, U22.6 (Cext)
unnamed: C20.1, R30.2, U22.7 (RCext)
unnamed: U23.2 (CP), U39.9, U47.4
unnamed: U23.9 (Q7), U37.2
unnamed: TP2.1, U23.1 (~PL), U28.3 (C), U45.8
unnamed: U24.11 (Cp), U27.8 (Q3), U39.5
unnamed: U24.3 (D0), U25.3 (Q0)
unnamed: U24.4 (D1), U25.5 (Q2)
unnamed: U24.7 (D2), U25.10 (Q4)
unnamed: U24.8 (D3), U25.12 (Q6)
unnamed: U24.13 (D4), U25.13 (Q7)
unnamed: U24.14 (D5), U25.11 (Q5)
unnamed: U24.17 (D6), U25.6 (Q3)
unnamed: U24.18 (D7), U25.4 (Q1)
unnamed: U25.8 (CP), U37.6, U39.8
unnamed: U25.1 (DSA), U36.9
unnamed: U26.13 (Q1), U27.13 (CP), U47.5
unnamed: U26.1 (~MR), U39.6
unnamed: U27.1 (CP), U46.13 (Q1), U47.6
unnamed: TP6.1, U27.2 (MR), U45.4
unnamed: U27.5 (Q2), U40.13
unnamed: U27.6 (Q3), U40.12
unnamed: TP5.1, U27.12 (MR), U40.8
unnamed: R40.1, TP4.1, U28.6 (~Q), U40.10
unnamed: C34.1, R40.2, U28.1 (~R)
unnamed: U28.8 (~Q), U28.12 (D)
unnamed: U29.6 (E2), U42.8
unnamed: U29.14 (~Y1), U44.13
unnamed: U29.13 (~Y2), U44.11
unnamed: C43.1, R51.2, U30.3 (C)
unnamed: U30.2 (D), U30.6 (~Q), U43.4, U43.12
unnamed: U30.5 (Q), U43.2, U43.9
unnamed: U31.11 (Cp), U43.3
unnamed: U31.1 (OE), U32.1 (OEa), U32.19 (OEb), U38.4
unnamed: U33.1 (OEa), U33.19 (OEb), U34.11 (Cp), U38.5, U43.8
unnamed: U34.1 (OE), U43.11
unnamed: U38.2, U38.3
unnamed: U38.6, U38.9
unnamed: U39.2, U40.1
unnamed: U39.10, U40.5
unnamed: U40.3, U42.1
unnamed: U42.13, U47.13
unnamed: U45.9, U45.10
unnamed: U40.11, U46.1 (~MR)
unnamed: R4.1, U101.15 (~Y0)
unnamed: R3.1, U101.14 (~Y1)
unnamed: R2.1, U101.13 (~Y2)
unnamed: R1.1, U101.12 (~Y3)
unnamed: C2.2, U102.14 (Cext)
unnamed: C2.1, R11.1, U102.15 (RCext)
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
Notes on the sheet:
Jumper to enable buzzer
IDE Interface
Spare
WDI I/O
Processor
Optional acoustic feedback (click on seek)
Serial-Parallel Conversion
Optional diode
Display & Sound
Pololu 5Volt (D24V22F5)
SELECTED
Resistor value up to user, depending on desired volume

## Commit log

2026-03-01 routing complete
2026-03-05 part replacement & autorouter complete
2026-03-28 3/28 updates
    swapped crystals for TH parts
2026-03-29 final modifications
2026-04-04 W2I-S100 Rev 1 Final
2026-04-04 Initial commit
    Added images of the PCB front and back renders to the README.
2026-04-20 First prototype photo
2026-04-20 Add prototype photo to README
    Added a photo of the first prototype to the README.
